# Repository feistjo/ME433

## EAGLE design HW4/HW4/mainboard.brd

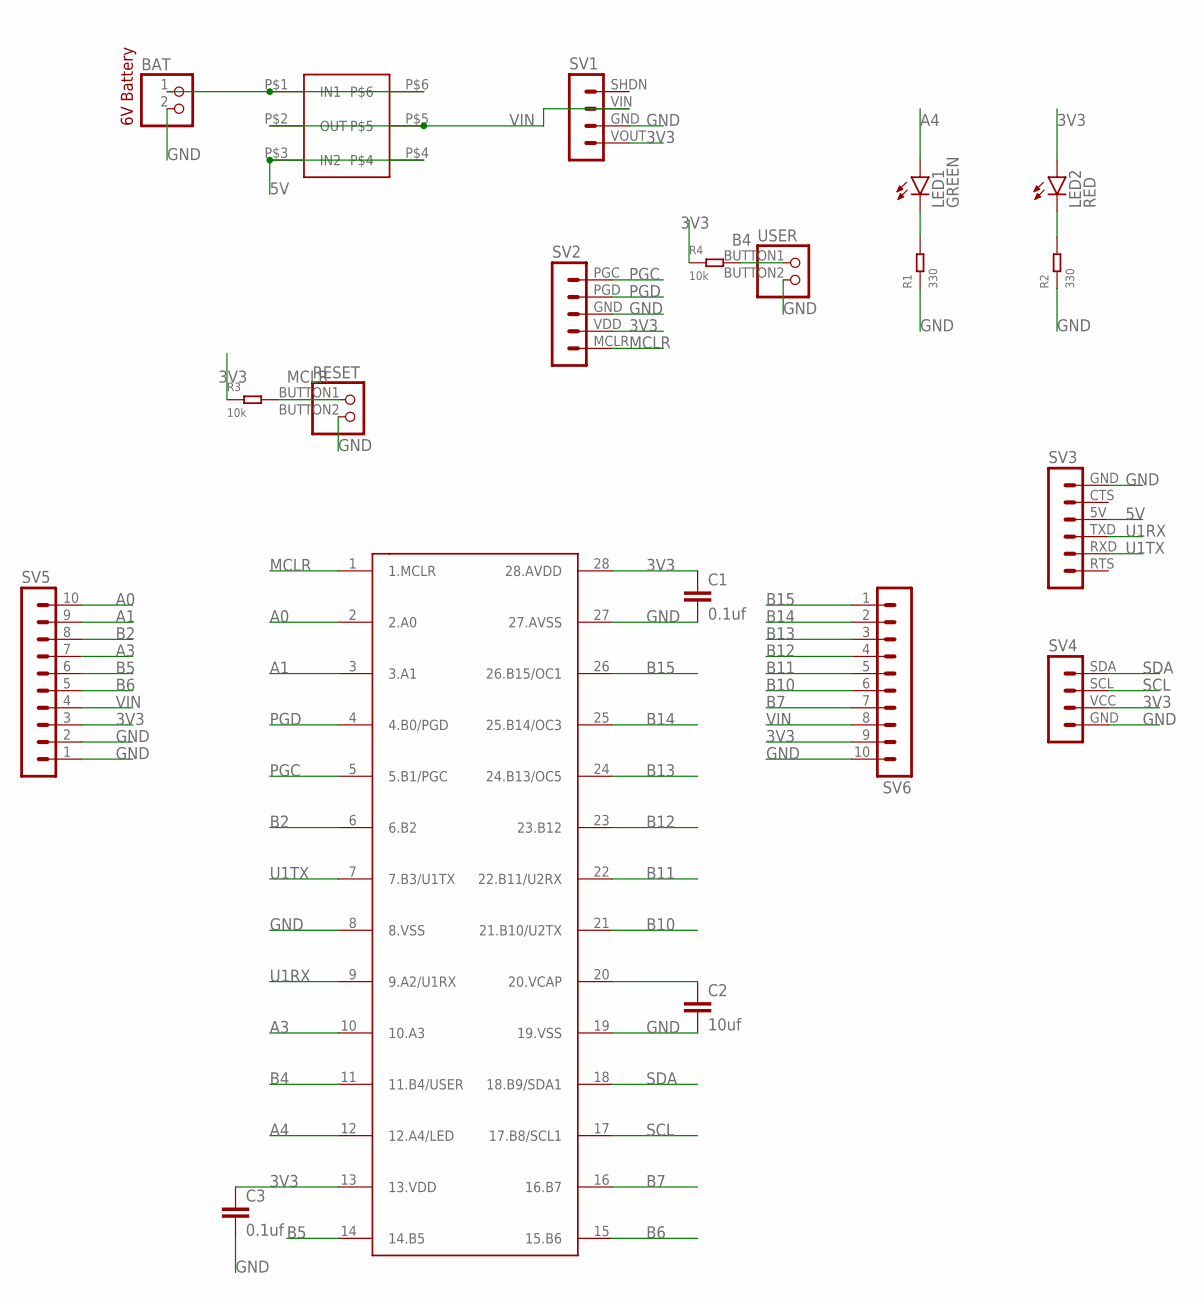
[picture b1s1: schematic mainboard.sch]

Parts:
BAT: PINHD-1X2; 1X02
C1, C3: 0.1uf; C2.5-3
C2: 10uf; C2.5-3
LED1: GREEN; LED3MM
LED2: RED; LED3MM
R1, R2: 330; PR-D2.3XL6.5MM
R3, R4: 10k; PR-D2.3XL6.5MM
RESET: PUSHBUTTON
SV1: POLOLU3.3POLOLU3.3; POLOLU3.3
SV2: MPLAB-SNAP
SV3: CP2104FRIEND
SV4: SSD1306
SV5, SV6: MA10-1
U$1: SLIDE_SWITCH; SLIDE
U$2: PIC32MX170F256B; DIL28-3
USER: PUSHBUTTON

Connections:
3V3: C1.1, C3.1, LED2.A, R3.1, R4.1, SV1.VOUT, SV2.VDD, SV4.VCC, SV5.3, SV6.9, U$2.13 (13.VDD), U$2.28 (28.AVDD)
5V: SV3.5V, U$1.P$3 (IN2), U$1.P$4
A0: SV5.10, U$2.2 (2.A0)
A1: SV5.9, U$2.3 (3.A1)
A3: SV5.7, U$2.10 (10.A3)
A4: LED1.A, U$2.12 (12.A4/LED)
B2: SV5.8, U$2.6 (6.B2)
B4: R4.2, U$2.11 (11.B4/USER), USER.BUTTON1 (1)
B5: SV5.6, U$2.14 (14.B5)
B6: SV5.5, U$2.15 (15.B6)
B7: SV6.7, U$2.16 (16.B7)
B10: SV6.6, U$2.21 (21.B10/U2TX)
B11: SV6.5, U$2.22 (22.B11/U2RX)
B12: SV6.4, U$2.23 (23.B12)
B13: SV6.3, U$2.24 (24.B13/OC5)
B14: SV6.2, U$2.25 (25.B14/OC3)
B15: SV6.1, U$2.26 (26.B15/OC1)
GND: BAT.2, C1.2, C2.2, C3.2, R1.1, R2.1, RESET.BUTTON2 (2), SV1.GND, SV2.GND, SV3.GND, SV4.GND, SV5.1, SV5.2, SV6.10, U$2.8 (8.VSS), U$2.19 (19.VSS), U$2.27 (27.AVSS), USER.BUTTON2 (2)
MCLR: R3.2, RESET.BUTTON1 (1), SV2.MCLR, U$2.1 (1.MCLR)
unnamed: BAT.1, U$1.P$1 (IN1), U$1.P$6
unnamed: LED1.K (C), R1.2
unnamed: LED2.K (C), R2.2
unnamed: C2.1, U$2.20 (20.VCAP)
PGC: SV2.PGC, U$2.5 (5.B1/PGC)
PGD: SV2.PGD, U$2.4 (4.B0/PGD)
SCL: SV4.SCL, U$2.17 (17.B8/SCL1)
SDA: SV4.SDA, U$2.18 (18.B9/SDA1)
U1RX: SV3.TXD, U$2.9 (9.A2/U1RX)
U1TX: SV3.RXD, U$2.7 (7.B3/U1TX)
VIN: SV1.VIN, SV5.4, SV6.8, U$1.P$2 (OUT), U$1.P$5

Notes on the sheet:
6V Battery

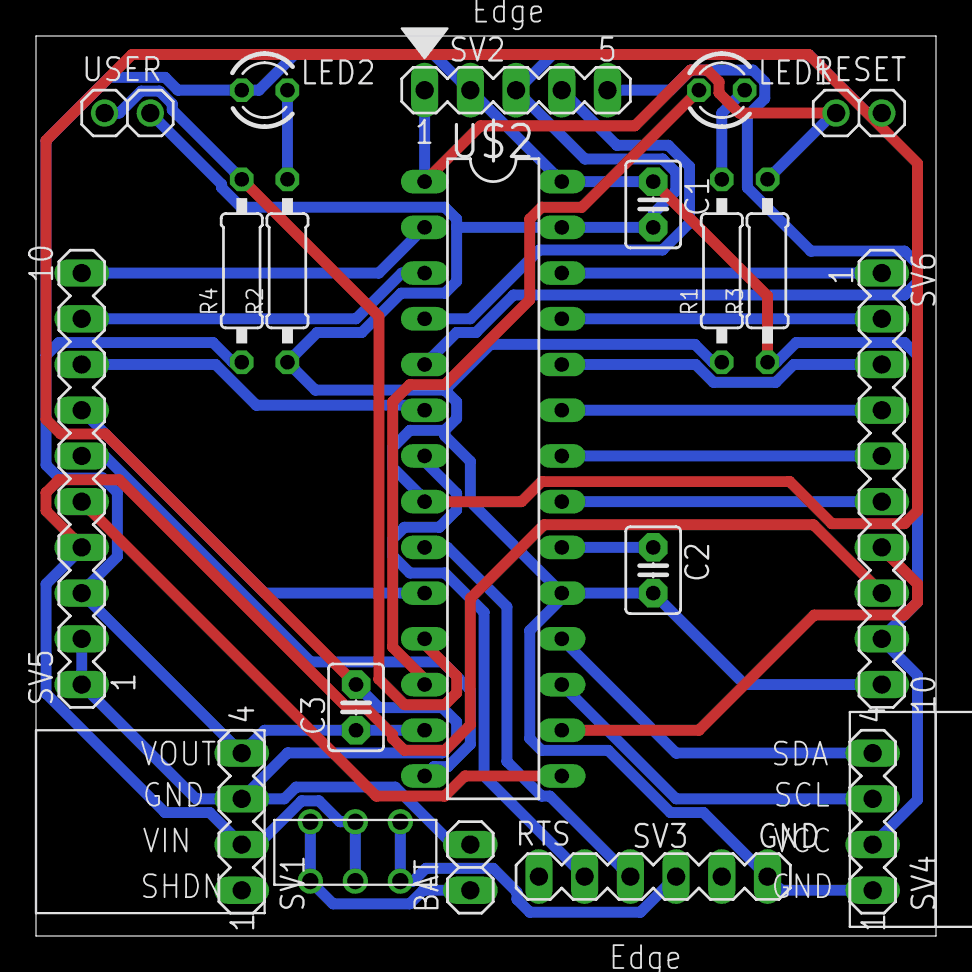
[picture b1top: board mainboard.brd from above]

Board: 2 copper layers, 50.0 x 50.0 mm, 20 parts (0 on the bottom side), 30 nets.

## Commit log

2022-04-04 HW2 schematic
2022-04-10 HW4 PCB
2022-05-17 HW10
2022-06-06 HW11
